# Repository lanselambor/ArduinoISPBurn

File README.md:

# Arduino ISP programmer  <br>
Using Arduino Mega 2560 burning bootloader to another Arduino board.<br>

## Usage <br>
### **1.Board assambling** <br>
* Arduino Mega2560 + SD card Shield + Base Shield <br>

### **2.Download and unzip*** <br>
* Download this repository.
* Unzip files within the folder libraries out to Arduino libraries.

### **3.Operation** <br>
* SD card init successfully with Green led on. <br>
* Press button roll to change program. <br>
* Press button start to begin burning program. <br>
* Red led on while burning. <br>
* Red led off and green led on if burning succeeded.

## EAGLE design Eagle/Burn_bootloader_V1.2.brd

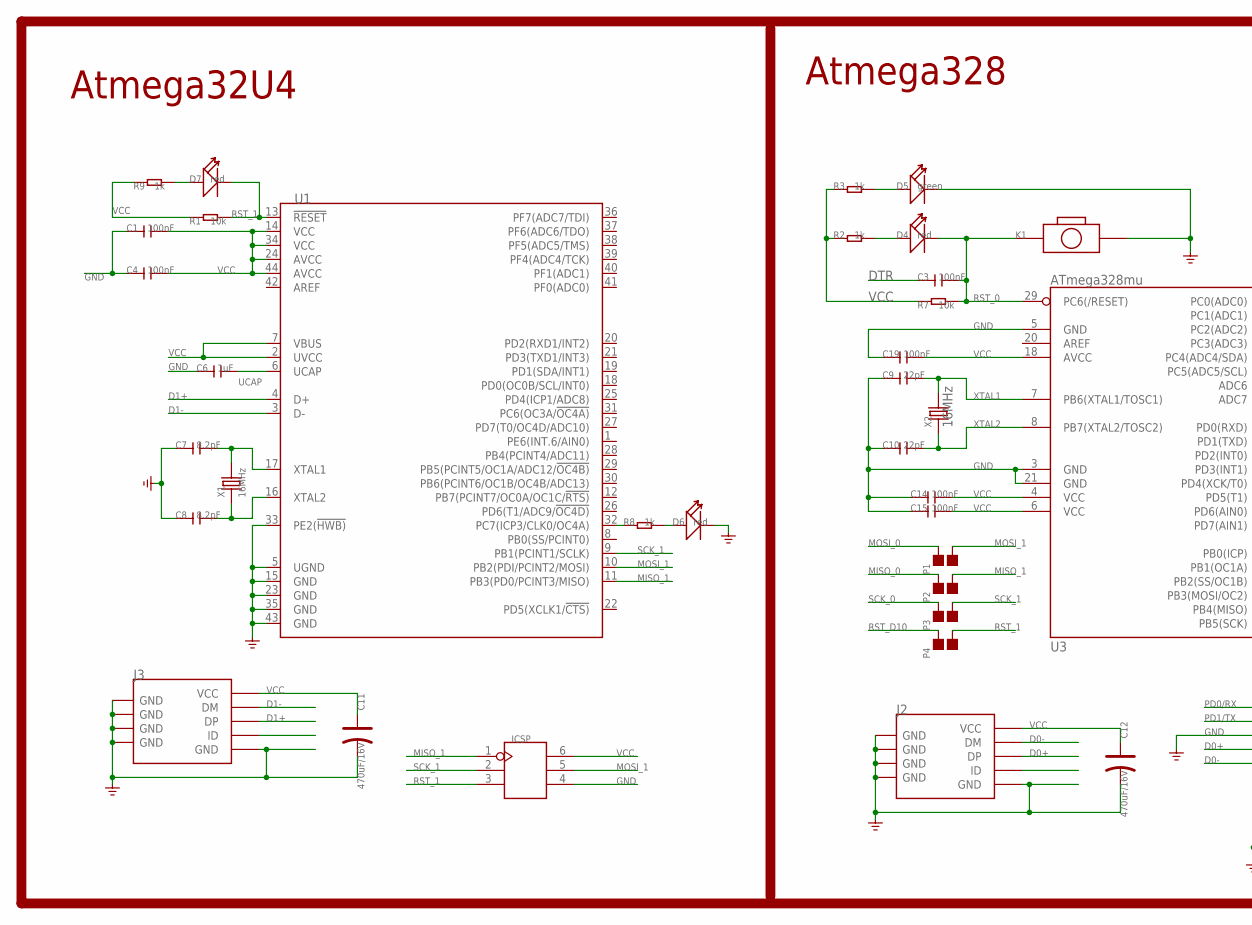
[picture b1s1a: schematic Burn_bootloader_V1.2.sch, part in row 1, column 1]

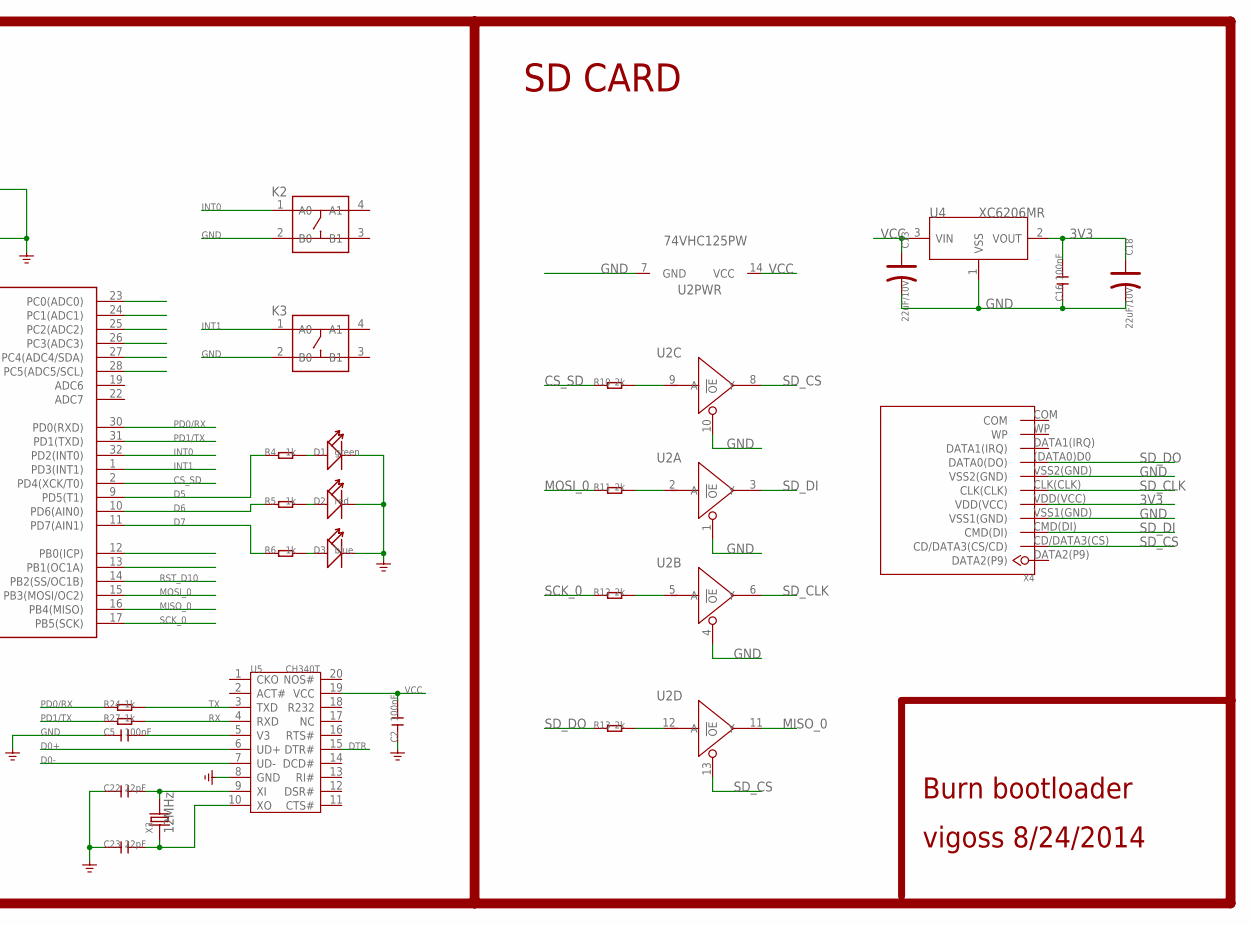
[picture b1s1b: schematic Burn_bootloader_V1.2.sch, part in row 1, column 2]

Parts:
C1, C2, C3, C4, C5, C14, C15, C19: 100nF; C0603
C6: 1uF; C0603
C7, C8: 8.2pF; C0603
C9, C10, C22, C23: 22pF; C0603
C11, C12: 470uF/16V; AVX-C
C13, C18: 22uF/10V; AVX-A
C16: 100nF; C0805
D1: green; LED-2P-2.54-6MM
D2: red; LED-2P-2.54-6MM
D3: blue; LED-2P-2.54-6MM
D4, D6, D7: red; LED-0603
D5: green; LED-0603
ICSP: HEADER-2X3P-2.54; 2X3P-2.54
J2, J3: USB-MINIUSB-5P-STRONG; MINI-SMD-5P
K1: BUTTON-2P'TS-1101F'; 2P-3.4X6.0X3.55H-90D
K2, K3: BUTTON-4P-6.2X6.2; 4P-6.2X6.2
P1, P2, P3, P4: PAD-JUMPER-2P; 2P-SMD-1.78X1.27
R1, R7: 10k; R0603
R2, R3, R4, R5, R6, R8, R9, R24, R27: 1k; R0603
R10, R11, R12, R13: 2k; R0603
U1: MCU-ATMEGA32U4; TEST-VQFN-44
U2: 74VHC125PW; TSSOP14
U3: ATmega328mu; TQFP32
U4: XC6206MR; SOT23
U5: CH340T; SSOP20
X1, X2: 16MHz; 2P-SMD-5X3.2
X3: 12MHz; 2P-SMD-5X3.2
X4: SDCARDEXTDEVICE; SDCARDEXTPACKAGE

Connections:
3V3: C16.2, C18.+, U4.2 (VOUT), X4.VDD(VCC)
CS_SD: R10.1, U3.2 (PD4(XCK/T0))
D0+: J2.3 (DP), U5.6 (UD+)
D0-: J2.2 (DM), U5.7 (UD-)
D1+: J3.3 (DP), U1.4 (D+)
D1-: J3.2 (DM), U1.3 (D-)
D5: R4.1, U3.9 (PD5(T1))
D6: R5.1, U3.10 (PD6(AIN0))
D7: R6.1, U3.11 (PD7(AIN1))
DTR: C3.1, U5.15 (DTR#)
GND: C1.1, C2.1, C4.1, C5.1, C6.1, C7.1, C8.1, C9.1, C10.1, C11.-, C12.-, C13.-, C14.1, C15.1, C16.1, C18.-, C19.1, C22.1, C23.1, D1.-, D2.-, D3.-, D5.-, D6.-, ICSP.4, J2.5 (GND), J2.GND@1 (GND), J2.GND@2 (GND), J2.GND@3 (GND), J2.GND@4 (GND), J3.5 (GND), J3.GND@1 (GND), J3.GND@2 (GND), J3.GND@3 (GND), J3.GND@4 (GND), K1.P$2 (2), K2.2 (B0), K3.2 (B0), U1.5 (UGND), U1.15 (GND), U1.23 (GND), U1.33 (PE2(!HWB)), U1.35 (GND), U1.43 (GND), U2.1 (!OE), U2.4 (!OE), U2.7 (GND), U2.10 (!OE), U3.3 (GND), U3.5 (GND), U3.21 (GND), U4.1 (VSS), U5.8 (GND), X4.VSS1(GND), X4.VSS2(GND)
INT0: K2.1 (A0), U3.32 (PD2(INT0))
INT1: K3.1 (A0), U3.1 (PD3(INT1))
MISO_0: P2.2, U2.11 (Y), U3.16 (PB4(MISO))
MISO_1: ICSP.1, P2.1, U1.11 (PB3(PD0/PCINT3/MISO))
MOSI_0: P1.2, R11.1, U3.15 (PB3(MOSI/OC2))
MOSI_1: ICSP.5, P1.1, U1.10 (PB2(PDI/PCINT2/MOSI))
unnamed: D1.+, R4.2
unnamed: D2.+, R5.2
unnamed: D4.+, R2.2
unnamed: D5.+, R3.2
unnamed: D3.+, R6.2
unnamed: R8.1, U1.32 (PC7(ICP3/CLK0/OC4A))
unnamed: D6.+, R8.2
unnamed: D7.+, R9.2
unnamed: C7.2, U1.17 (XTAL1), X1.2
unnamed: C8.2, U1.16 (XTAL2), X1.1
unnamed: R13.2, U2.12 (A)
unnamed: R12.2, U2.5 (A)
unnamed: R11.2, U2.2 (A)
unnamed: R10.2, U2.9 (A)
unnamed: C22.2, U5.9 (XI), X3.2
unnamed: C23.2, U5.10 (XO), X3.1
PD0/RX: R24.1, U3.30 (PD0(RXD))
PD1/TX: R27.1, U3.31 (PD1(TXD))
RST_0: C3.2, D4.-, K1.P$1 (1), R7.2, U3.29 (PC6(/RESET))
RST_1: D7.-, ICSP.3, P4.1, R1.2, U1.13 (!RESET)
RST_D10: P4.2, U3.14 (PB2(SS/OC1B))
RX: R27.2, U5.4 (RXD)
SCK_0: P3.2, R12.1, U3.17 (PB5(SCK))
SCK_1: ICSP.2, P3.1, U1.9 (PB1(PCINT1/SCLK))
SD_CLK: U2.6 (Y), X4.CLK(CLK)
SD_CS: U2.8 (Y), U2.13 (!OE), X4.CD/DATA3(CS) (CD/DATA3(CS/CD))
SD_DI: U2.3 (Y), X4.CMD(DI)
SD_DO: R13.1, X4.(DATA0)D0 (DATA0(DO))
TX: R24.2, U5.3 (TXD)
UCAP: C6.2, U1.6 (UCAP)
V3: C5.2, U5.5 (V3)
VCC: C1.2, C2.2, C4.2, C11.+, C12.+, C13.+, C14.2, C15.2, C19.2, ICSP.6, J2.1 (VCC), J3.1 (VCC), R1.1, R2.1, R3.1, R7.1, R9.1, U1.2 (UVCC), U1.7 (VBUS), U1.14 (VCC), U1.24 (AVCC), U1.34 (VCC), U1.44 (AVCC), U2.14 (VCC), U3.4 (VCC), U3.6 (VCC), U3.18 (AVCC), U4.3 (VIN), U5.19 (VCC)
XTAL1: C9.2, U3.7 (PB6(XTAL1/TOSC1)), X2.2
XTAL2: C10.2, U3.8 (PB7(XTAL2/TOSC2)), X2.1

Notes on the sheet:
Atmega32U4
Atmega328
SD CARD
Burn bootloader
vigoss 8/24/2014

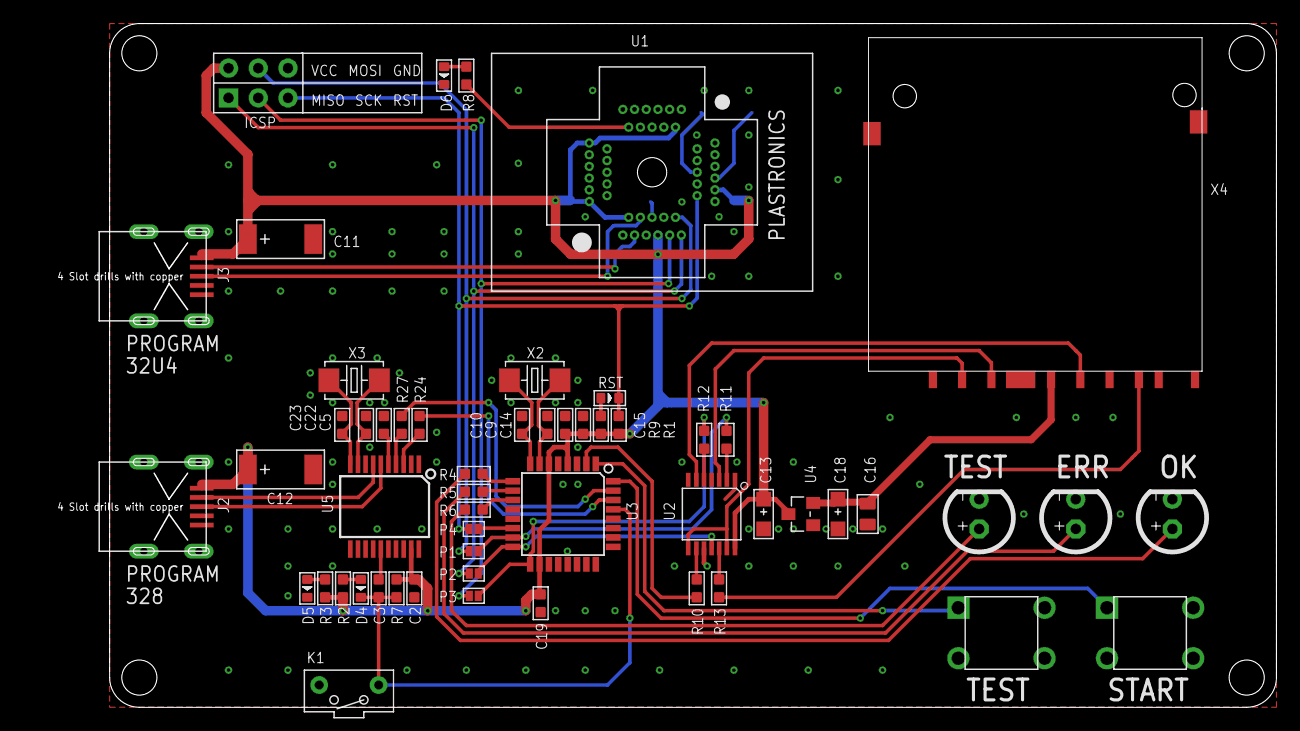
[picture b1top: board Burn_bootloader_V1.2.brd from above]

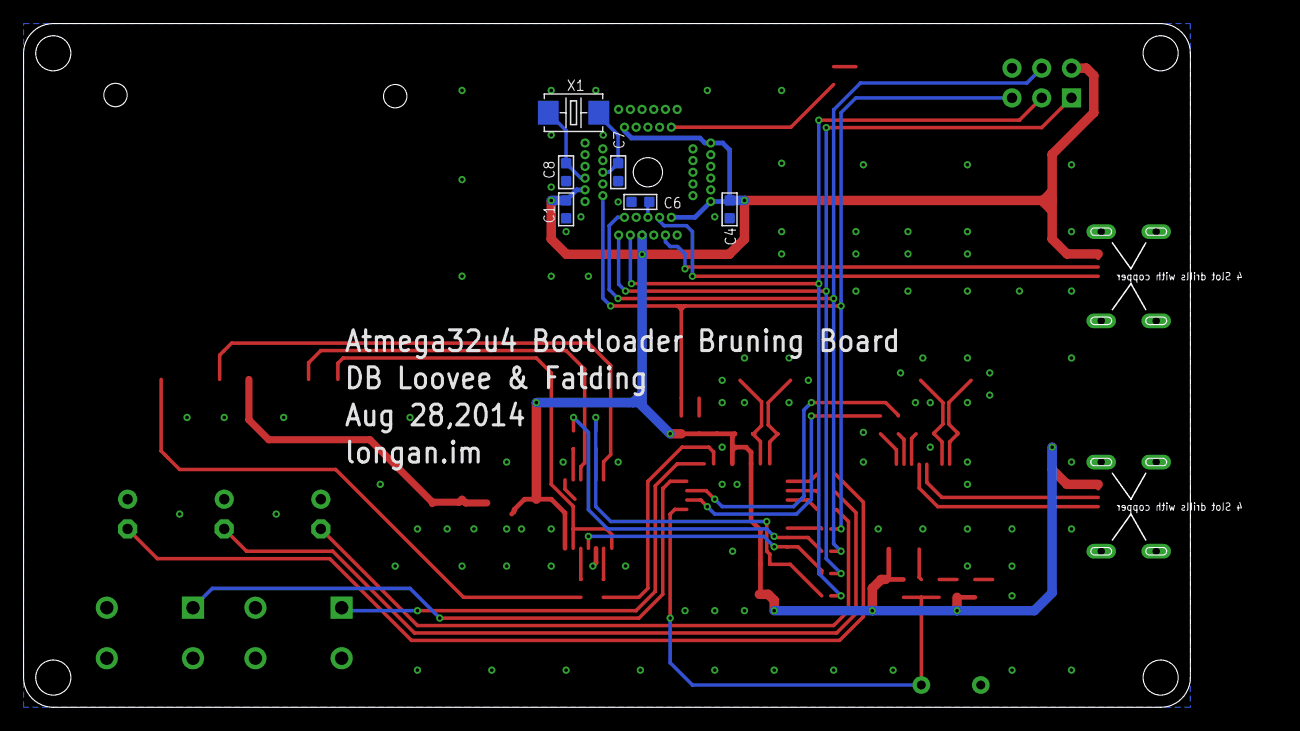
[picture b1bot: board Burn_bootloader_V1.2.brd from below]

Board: 2 copper layers, 106.9 x 58.3 mm, 61 parts (6 on the bottom side), 51 nets.

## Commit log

2015-06-30 :space_invader: Added .gitattributes & .gitignore files
2015-06-30 initial
